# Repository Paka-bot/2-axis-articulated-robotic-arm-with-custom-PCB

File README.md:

(https://projects.engineering.oregonstate.edu/projects/?id=NPUBsuqH4jg9Jg8b)

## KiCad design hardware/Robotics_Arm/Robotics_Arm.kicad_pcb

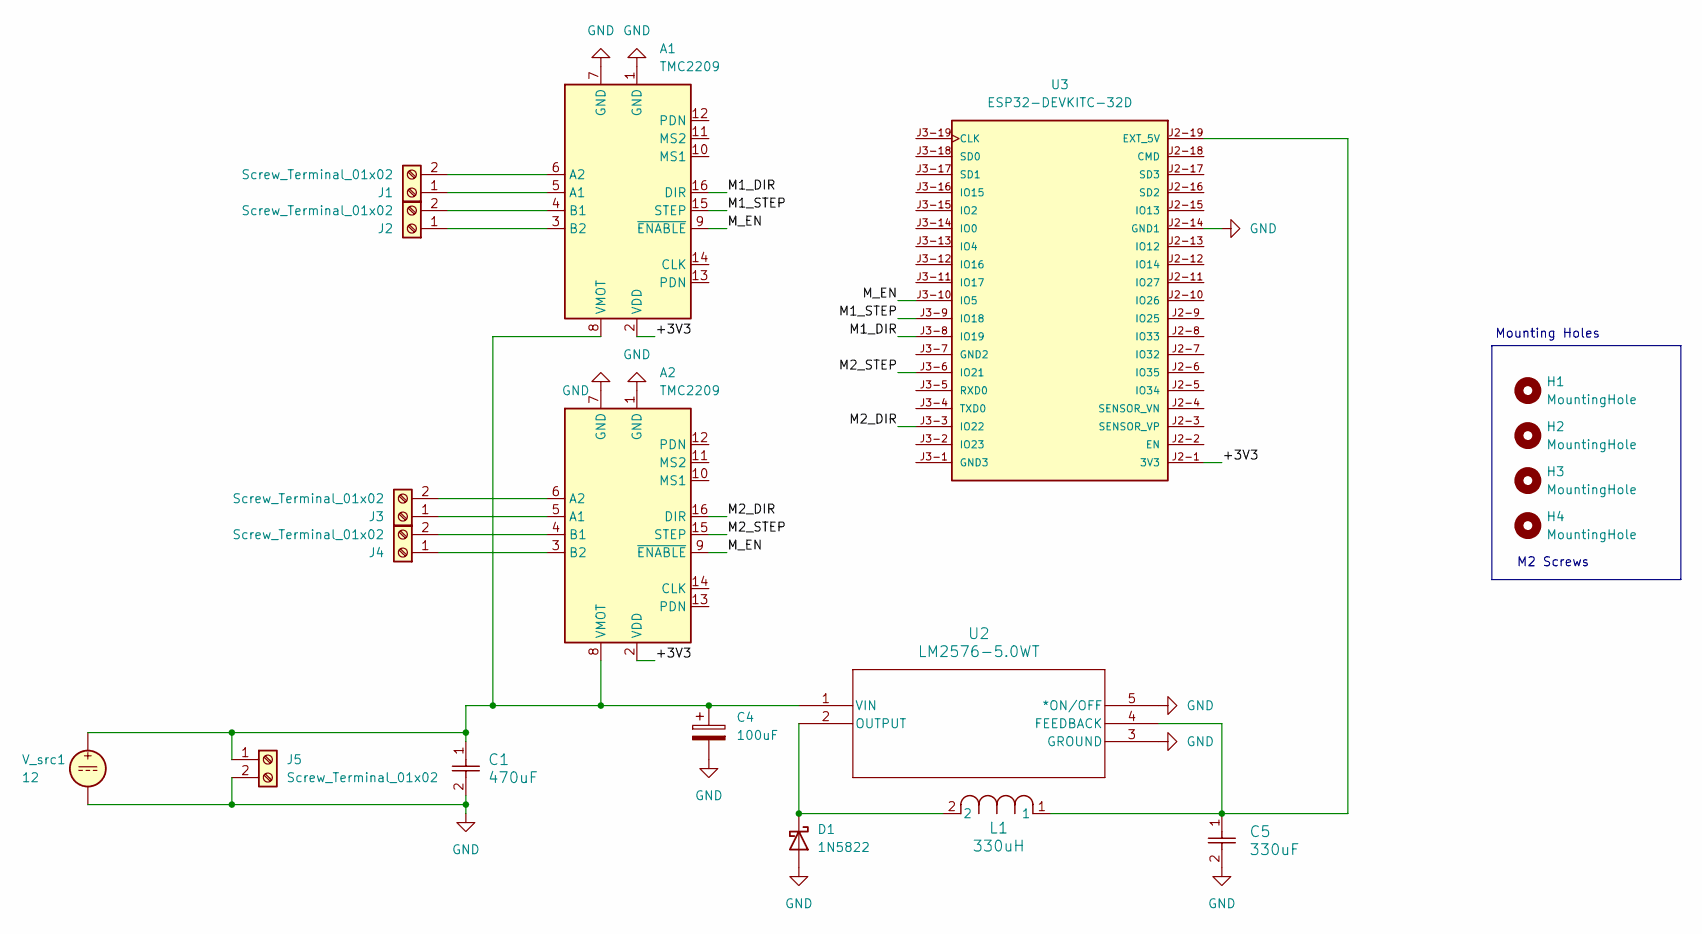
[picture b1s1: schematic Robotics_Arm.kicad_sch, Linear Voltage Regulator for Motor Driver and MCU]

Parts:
A1, A2: TMC2209; Pololu_Breakout-16_15.2x20.3mm
C1: 470uF; CAP_10 X 16_NCH
C4: 100uF; CP_Radial_D5.0mm_P2.00mm
C5: 330uF; CAP_PAN_10X12.5_PAN
D1: 1N5822
H1, H2, H3, H4: MountingHole; MountingHole_2.2mm_M2
J1, J2, J3, J4, J5: Screw_Terminal_01x02; TerminalBlock_TE_282834-2_1x02_P2.54mm_Horizontal
L1: 330uH; IND_PE-53117NL_PUL
U2: LM2576-5.0WT; TO-220-5_P3.4x3.7mm_StaggerEven_Lead3.8mm_Vertical
U3: ESP32-DEVKITC-32D; MODULE_ESP32-DEVKITC-32D; PARTREV V4
V_src1: 12

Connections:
/+3V3: A1.2 (VDD), A2.2 (VDD), U3.J2-1 (3V3)
/M1_DIR: A1.16 (DIR), U3.J3-8 (IO19)
/M1_STEP: A1.15 (STEP), U3.J3-9 (IO18)
/M2_DIR: A2.16 (DIR), U3.J3-3 (IO22)
/M2_STEP: A2.15 (STEP), U3.J3-6 (IO21)
/M_EN: A1.9 (~ENABLE), A2.9 (~ENABLE), U3.J3-10 (IO5)
GND: A1.1 (GND), A1.7 (GND), A2.1 (GND), A2.7 (GND), C1.2, C4.2, C5.2, D1.2 (A), J5.2, U2.3 (GROUND), U2.5 (*ON/OFF), U3.J2-14 (GND1), V_src1.2
unnamed: A1.5 (A1), J1.1
unnamed: A1.6 (A2), J1.2
unnamed: A1.4 (B1), J2.2
unnamed: A1.3 (B2), J2.1
unnamed: A1.8 (VMOT), A2.8 (VMOT), C1.1, C4.1, J5.1, U2.1 (VIN), V_src1.1
unnamed: A2.5 (A1), J3.1
unnamed: A2.6 (A2), J3.2
unnamed: A2.4 (B1), J4.2
unnamed: A2.3 (B2), J4.1
unnamed: D1.1 (K), L1.2, U2.2 (OUTPUT)
unnamed: C5.1, L1.1, U2.4 (FEEDBACK), U3.J2-19 (EXT_5V)

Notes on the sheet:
Mounting Holes
M2 Screws

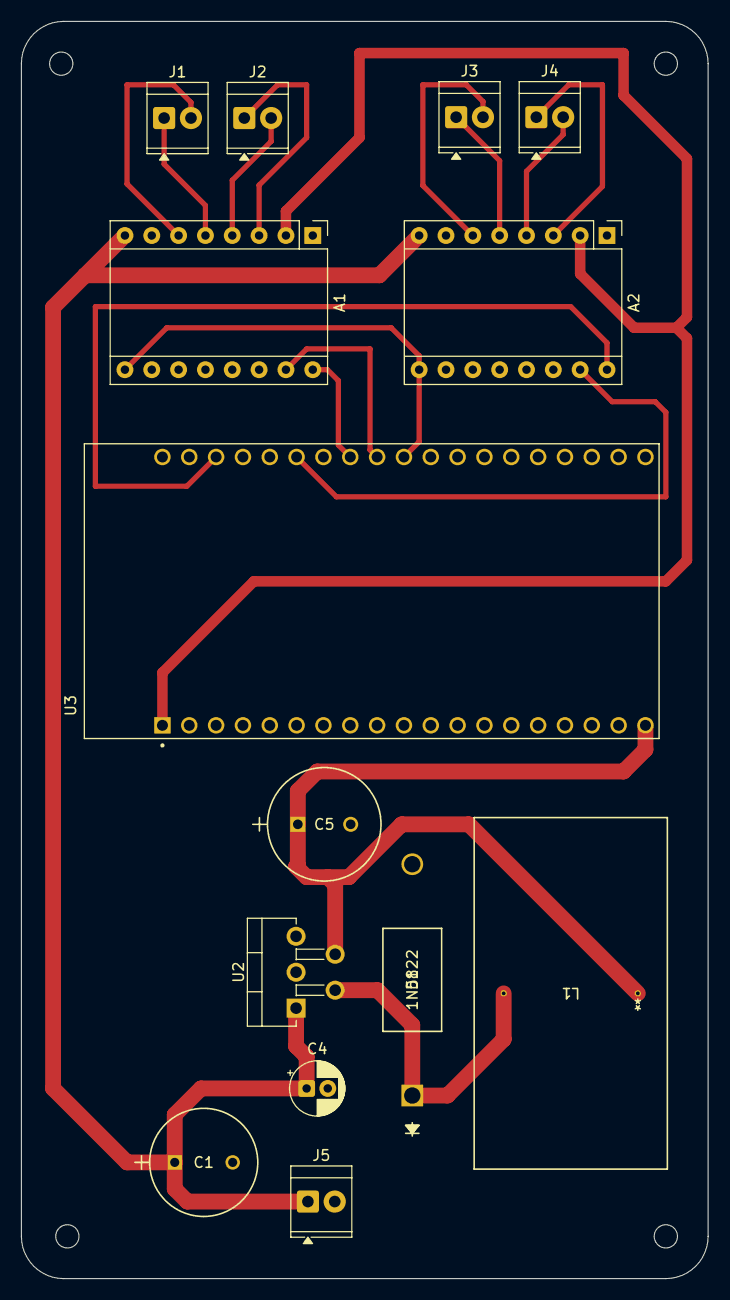
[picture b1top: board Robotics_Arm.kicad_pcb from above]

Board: 2 copper layers, 65.0 x 119.0 mm, 18 parts (0 on the bottom side), 18 nets.

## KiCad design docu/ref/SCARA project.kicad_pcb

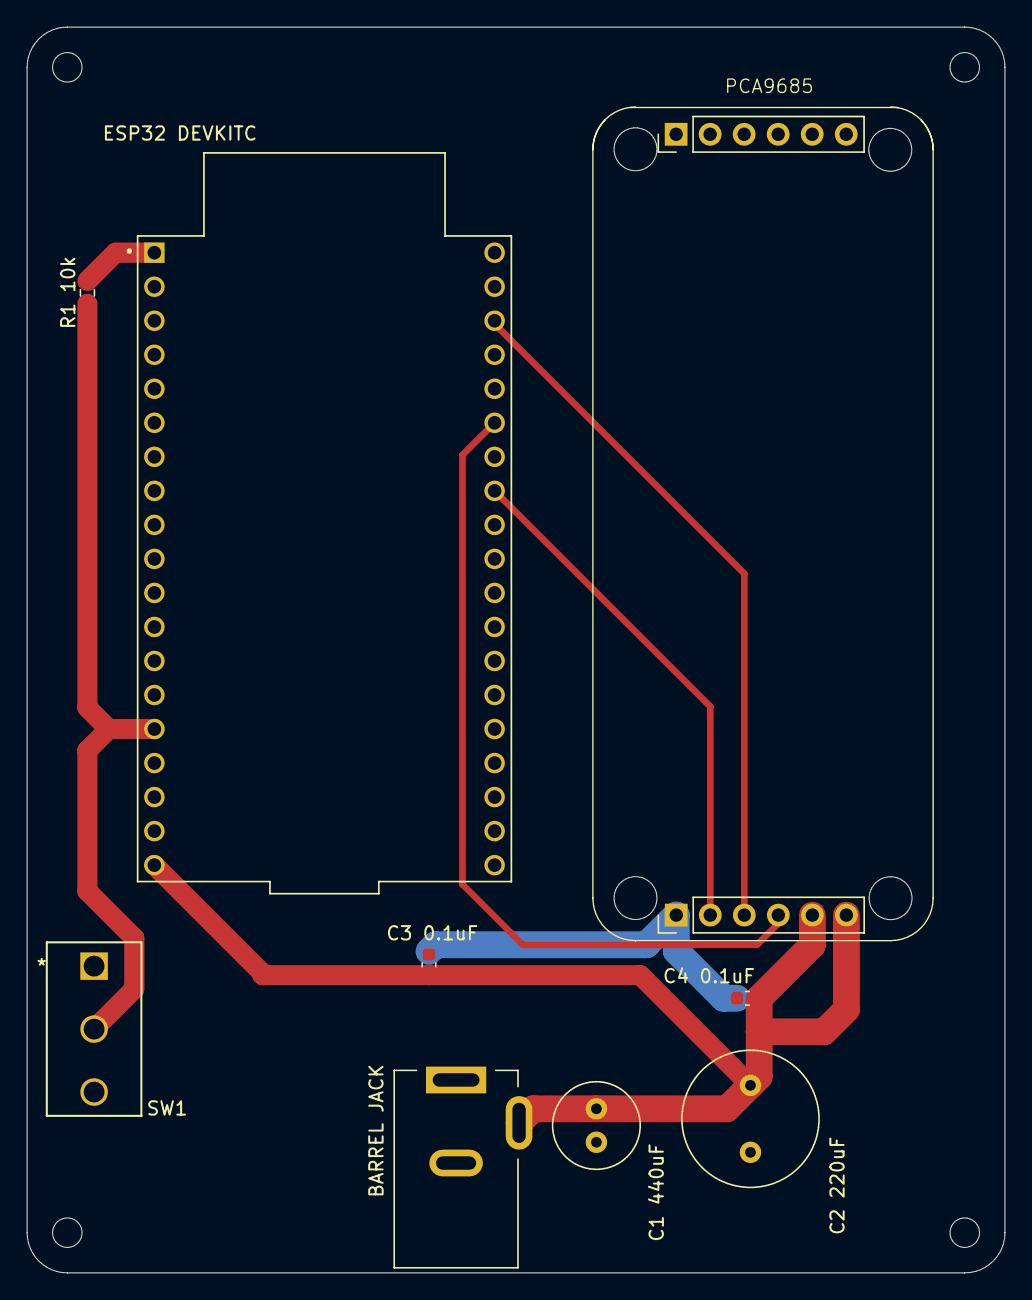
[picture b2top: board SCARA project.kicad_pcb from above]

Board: 2 copper layers, 73.0 x 93.0 mm, 18 parts (0 on the bottom side), 7 nets.

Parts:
BARREL JACK: DCJ235-05-A-K1-K; BarrelJack_Kycon_KLDX-0202-xC_Horizontal
C1 440uF: 470uF; C_Radial_D6.3mm_H7.0mm_P2.50mm
C2 220uF: 220uF; C_Radial_D10.0mm_H12.5mm_P5.00mm
C3 0.1uF, C4 0.1uF: 0.1uF; C_0603_1608Metric
ESP32 DEVKITC: ESP32-DEVKITC; MODULE_ESP32-DEVKITC
H1, H2, H3, H4: MountingHole; MountingHole_2.2mm_M2
H5, H6, H7, H8: MountingHole; MountingHole_3.2mm_M3
J1, J2: Conn_01x06_Socket; PinHeader_1x06_P2.54mm_Vertical
R1 10k: 10k; R_0603_1608Metric
SW1: SLW-1276864-4A-D; SLW-1276864_CUD

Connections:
GND: BARREL JACK.2, C1 440uF.2, C2 220uF.2, C3 0.1uF.2, C4 0.1uF.2, ESP32 DEVKITC.14 (GND1), J2.1, SW1.1
unnamed: ESP32 DEVKITC.31 (IO19), J2.2
unnamed: ESP32 DEVKITC.36 (IO22), J2.3
unnamed: ESP32 DEVKITC.33 (IO21), J2.4
unnamed: BARREL JACK.3, C1 440uF.1, C2 220uF.1, C3 0.1uF.1, C4 0.1uF.1, ESP32 DEVKITC.19 (EXT_5V), J2.5, J2.6
unnamed: ESP32 DEVKITC.1 (3V3), R1 10k.2
unnamed: ESP32 DEVKITC.15 (IO13), R1 10k.1, SW1.2

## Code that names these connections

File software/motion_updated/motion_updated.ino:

#include <math.h>

#define M1_STEP 18
#define M1_DIR  19
#define M2_STEP 21
#define M2_DIR  22
#define M_EN    5

const float STEPS_PER_REV = 1600.0; 
const int SPEED_DELAY = 3000; 

long current_step1 = 0; 
long current_step2 = 0;

void setup() {
  Serial.begin(115200);
  pinMode(M1_STEP, OUTPUT); pinMode(M1_DIR, OUTPUT);
  pinMode(M2_STEP, OUTPUT); pinMode(M2_DIR, OUTPUT);
  pinMode(M_EN, OUTPUT);
  digitalWrite(M_EN, LOW);
  Serial.println("Ready");
}

void loop() {
  if (Serial.available() > 0) {
    String cmd = Serial.readStringUntil('\n');
    cmd.trim(); cmd.toUpperCase();
    
    if (cmd == "M2") { digitalWrite(M_EN, HIGH); Serial.println("OFF"); return; }
    if (cmd == "M6") { digitalWrite(M_EN, LOW); Serial.println("ON"); return; }
    
    if (cmd.indexOf("M1") != -1 && cmd.indexOf("M2") != -1) {
      float v1 = parseVal(cmd, "M1");
      float v2 = parseVal(cmd, "M2");
      moveSimultaneous(v1, v2);
    }
  }
}

float parseVal(String cmd, String key) {
  int idx = cmd.indexOf(key);
  int next = cmd.indexOf(' ', idx + 3);
  return cmd.substring(idx + 3, next == -1 ? cmd.length() : next).toFloat();
}

void moveSimultaneous(float angle1, float angle2) {
  long target1 = current_step1 + round(angle1 * (STEPS_PER_REV / 360.0));
  long target2 = current_step2 + round(angle2 * (STEPS_PER_REV / 360.0));
  
  long d1 = target1 - current_step1;
  long d2 = target2 - current_step2;
  
  int dir1 = d1 > 0 ? HIGH : LOW;
  int dir2 = d2 > 0 ? LOW : HIGH;

  digitalWrite(M1_DIR, dir1);
  digitalWrite(M2_DIR, dir2);
  
  d1 = abs(d1); d2 = abs(d2);
  long max_steps = max(d1, d2);
  long c1 = max_steps / 2;
  long c2 = max_steps / 2;
  
  for(long i=0; i<max_steps; i++) {
    if (Serial.available() > 0) {
      String check = Serial.readStringUntil('\n');
      check.trim(); check.toUpperCase();
      if (check == "M2") { 
        digitalWrite(M_EN, HIGH);
        Serial.println("OFF");
        return;
      }
    }

    c1 -= d1;
    if(c1 < 0) { 
      digitalWrite(M1_STEP, HIGH); delayMicroseconds(2); digitalWrite(M1_STEP, LOW); 
      c1 += max_steps; 
    }
    c2 -= d2;
    if(c2 < 0) { 
      digitalWrite(M2_STEP, HIGH); delayMicroseconds(2); digitalWrite(M2_STEP, LOW); 
      c2 += max_steps; 
    }
    delayMicroseconds(SPEED_DELAY);
  }
  current_step1 = target1;
  current_step2 = target2;
  Serial.println("OK");
}

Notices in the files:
parts and their libraries:
Copyright 2016 Accelerated Designs. All rights reserved.
